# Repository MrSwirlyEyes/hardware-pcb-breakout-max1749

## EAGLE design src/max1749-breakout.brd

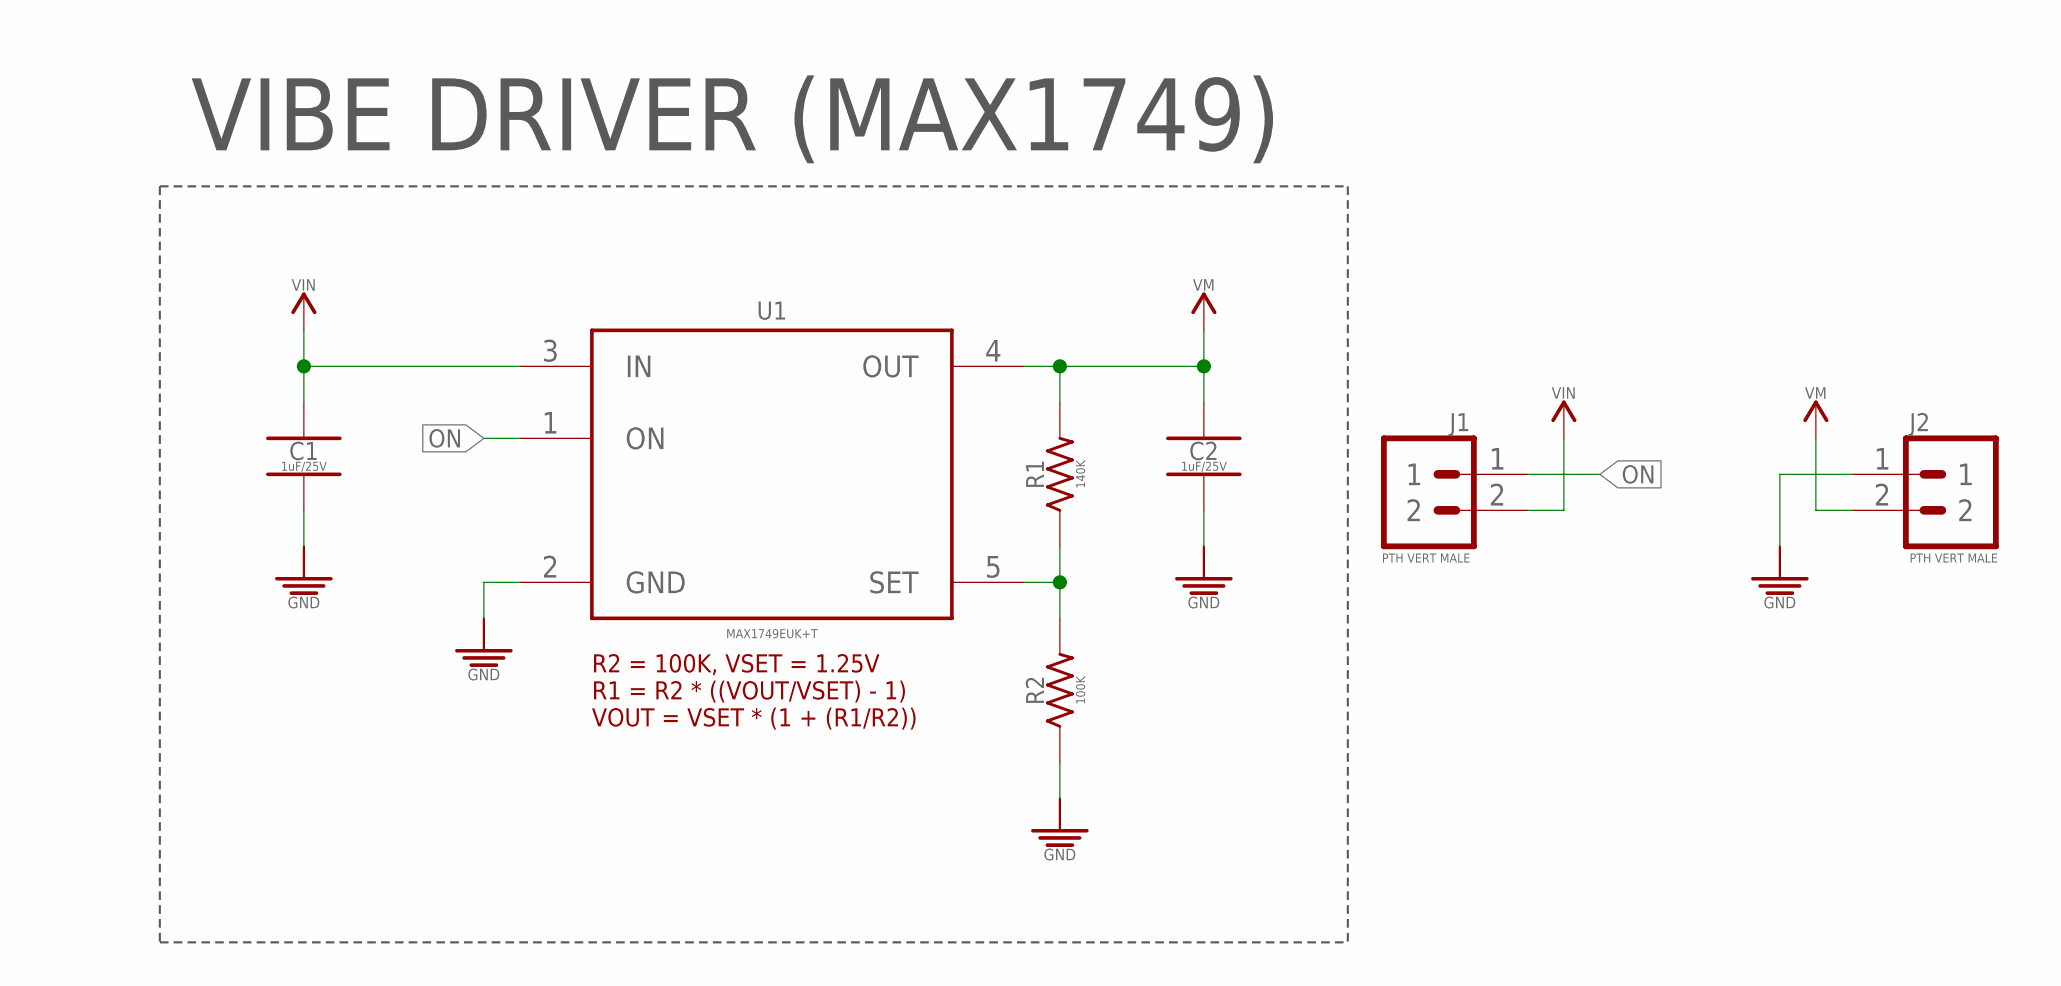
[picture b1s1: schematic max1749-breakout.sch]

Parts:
C1, C2: 1uF/25V; CAPC1005X55_SMD-0402
J1, J2: PTH VERT MALE; HDRV2W64P254_1X2_508X254X838B
R1: 140K; RESC1005X35_SMD-0402
R2: 100K; RESC1005X35_SMD-0402
U1: MAX1749EUK+T; SOT95P280X117-5N

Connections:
GND: C1.2, C2.2, J2.1, R2.1, U1.2 (GND)
unnamed: R1.1, R2.2, U1.5 (SET)
ON: J1.1, U1.1 (ON)
VIN: C1.1, J1.2, U1.3 (IN)
VM: C2.1, J2.2, R1.2, U1.4 (OUT)

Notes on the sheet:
VIBE DRIVER (MAX1749)

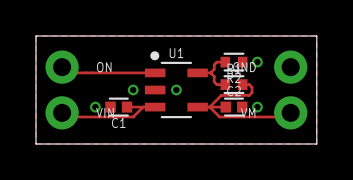
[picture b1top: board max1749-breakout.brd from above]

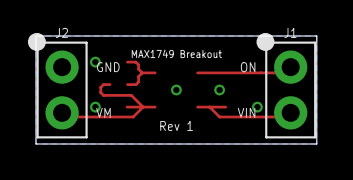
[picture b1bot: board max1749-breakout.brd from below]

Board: 2 copper layers, 15.6 x 6.0 mm, 7 parts (2 on the bottom side), 5 nets.

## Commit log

2021-01-12 [Rev 1] - Initialize repo.
2021-08-11 Update CAM files.
